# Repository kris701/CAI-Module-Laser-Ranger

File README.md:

# CAI-Module-Laser-Ranger
This is a project about making an extension module for my Snapmaker Original printer. This is also an extension to [another of my projects](https://github.com/kris701/CAI), and is directly connected to it. It is also designed to be mounted on my [toolhead extension project](https://github.com/kris701/SnapMaker-Toolhead-Extensions).
The purpose of this module is to making calibration of the Snapmaker Laser module easier, since it can be a bit of a pain to calibrate it every time you need to use it. Instead, this is a system where a little screen displays how far above the bed that the module is. This makes it a lot easier to calibrate is, as it removes the need to use that little calibration paper that comes with the printer.

The system consists of a little OLED screen, a infrared proximity sensor and two buttons to calibrate it. The buttons can be held down, to move the little triangle in the display up or down. The last set calibration value is saved in the EEPROM of the Arduino Nano that controls it, so that its not lost when the power goes off.

This then makes it so that you only really have to calibrate it once (with the calibration paper), and then you can just use the ranger module from there on out.

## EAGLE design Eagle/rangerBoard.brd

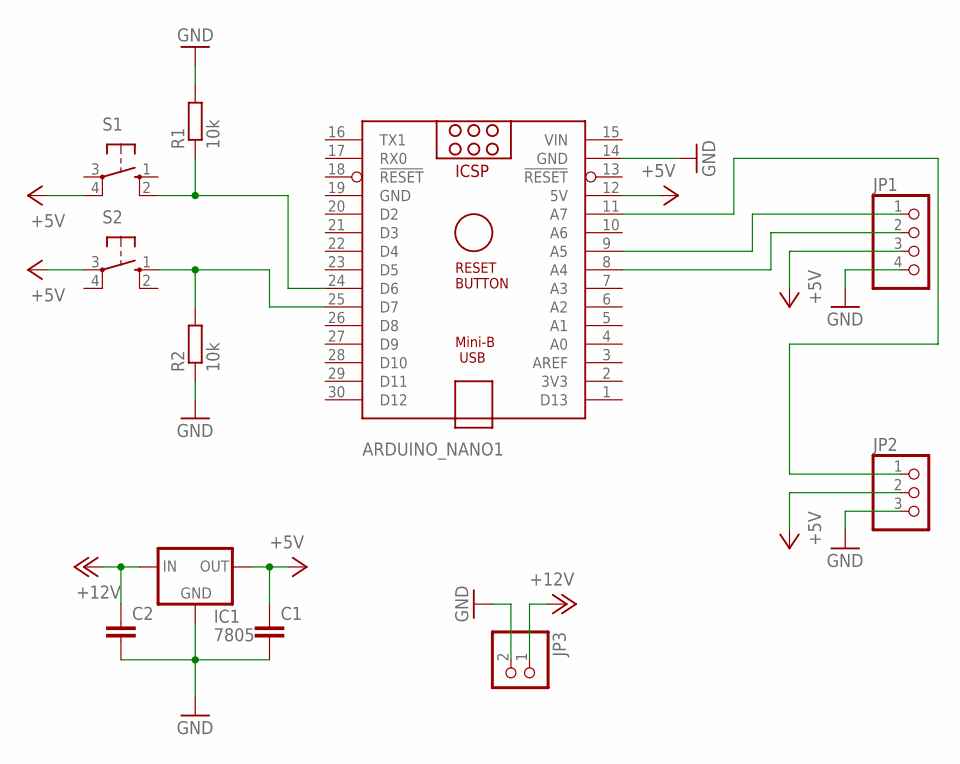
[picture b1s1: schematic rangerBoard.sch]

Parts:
ARDUINO_NANO1: ARDUINO_NANO
C1, C2: C5/7.2; C5B7.2
IC1: 7805; 78XXL
JP1: PINHD-1X4; 1X04
JP2: PINHD-1X3; 1X03
JP3: PINHD-1X2; 1X02
R1, R2: 10k; 0204/7
S1, S2: 10-XX; B3F-10XX

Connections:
+5V: ARDUINO_NANO1.12 (5V), C1.1, IC1.OUT, JP1.3, JP2.2, S1.4 (P1), S2.3
+12V: C2.1, IC1.IN, JP3.1
GND: ARDUINO_NANO1.14 (GND), ARDUINO_NANO1.19 (GND), C1.2, C2.2, IC1.GND, JP1.4, JP2.3, JP3.2, R1.2, R2.1
unnamed: ARDUINO_NANO1.24 (D6), R1.1, S1.2 (S1)
unnamed: ARDUINO_NANO1.25 (D7), R2.2, S2.1 (S)
unnamed: ARDUINO_NANO1.11 (A7), JP2.1
unnamed: ARDUINO_NANO1.8 (A4), JP1.2
unnamed: ARDUINO_NANO1.9 (A5), JP1.1
VIN: ARDUINO_NANO1.15 (VIN)

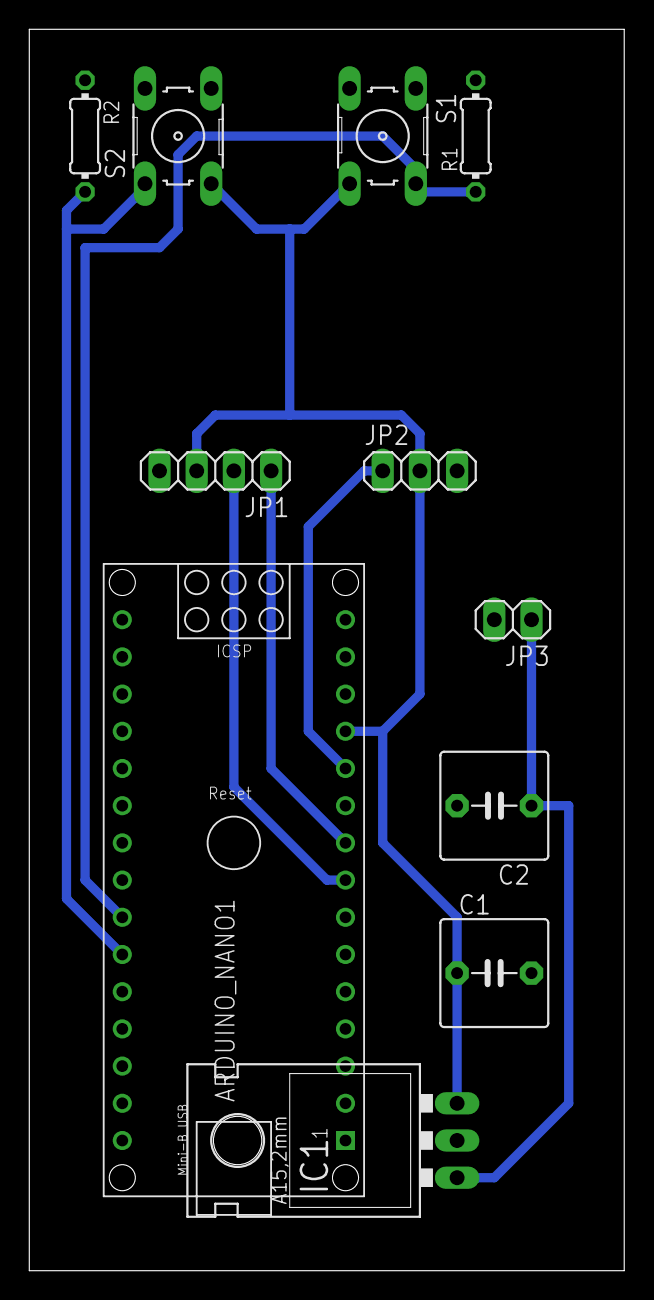
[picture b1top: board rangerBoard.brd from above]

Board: 2 copper layers, 40.6 x 84.8 mm, 11 parts (0 on the bottom side), 8 nets.

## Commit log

2021-12-14 Add .gitignore and .gitattributes.
2021-12-14 Added base code
2021-12-14 Added a baseline code
2021-12-14 Added first eagle drawings
2021-12-14 Removed G-Code files from the repo
2021-12-27 * Updated code * Added models
2021-12-27 Added STL Files for printing
2021-12-27 Added the printing config
